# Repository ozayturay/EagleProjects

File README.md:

View this project on [CADLAB.io](https://cadlab.io/project/1437). 

# EagleProjects
Eagle Projects by Özay Turay a.k.a Simon/CGTr

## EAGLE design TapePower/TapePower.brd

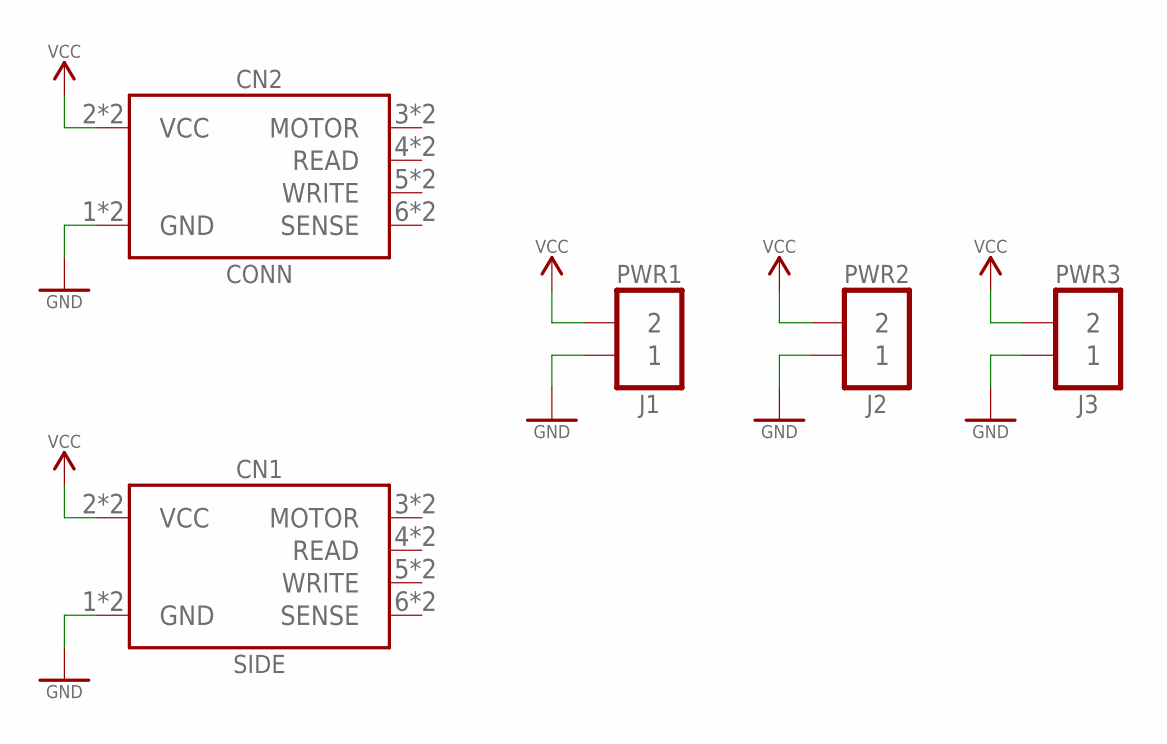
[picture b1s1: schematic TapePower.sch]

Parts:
CN1: SIDE; C64_TAPE_SIDE
CN2: CONN; C64_TAPE_PADS
J1: PWR1; HDR_1X02
J2: PWR2; HDR_1X02
J3: PWR3; HDR_1X02

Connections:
GND: CN1.1 (GND), CN1.A (GND), CN2.1 (GND), CN2.A (GND), J1.1, J2.1, J3.1
VCC: CN1.2 (VCC), CN1.B (VCC), CN2.2 (VCC), CN2.B (VCC), J1.2, J2.2, J3.2

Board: 2 copper layers, 5 parts (0 on the bottom side), 2 nets, no tracks yet.

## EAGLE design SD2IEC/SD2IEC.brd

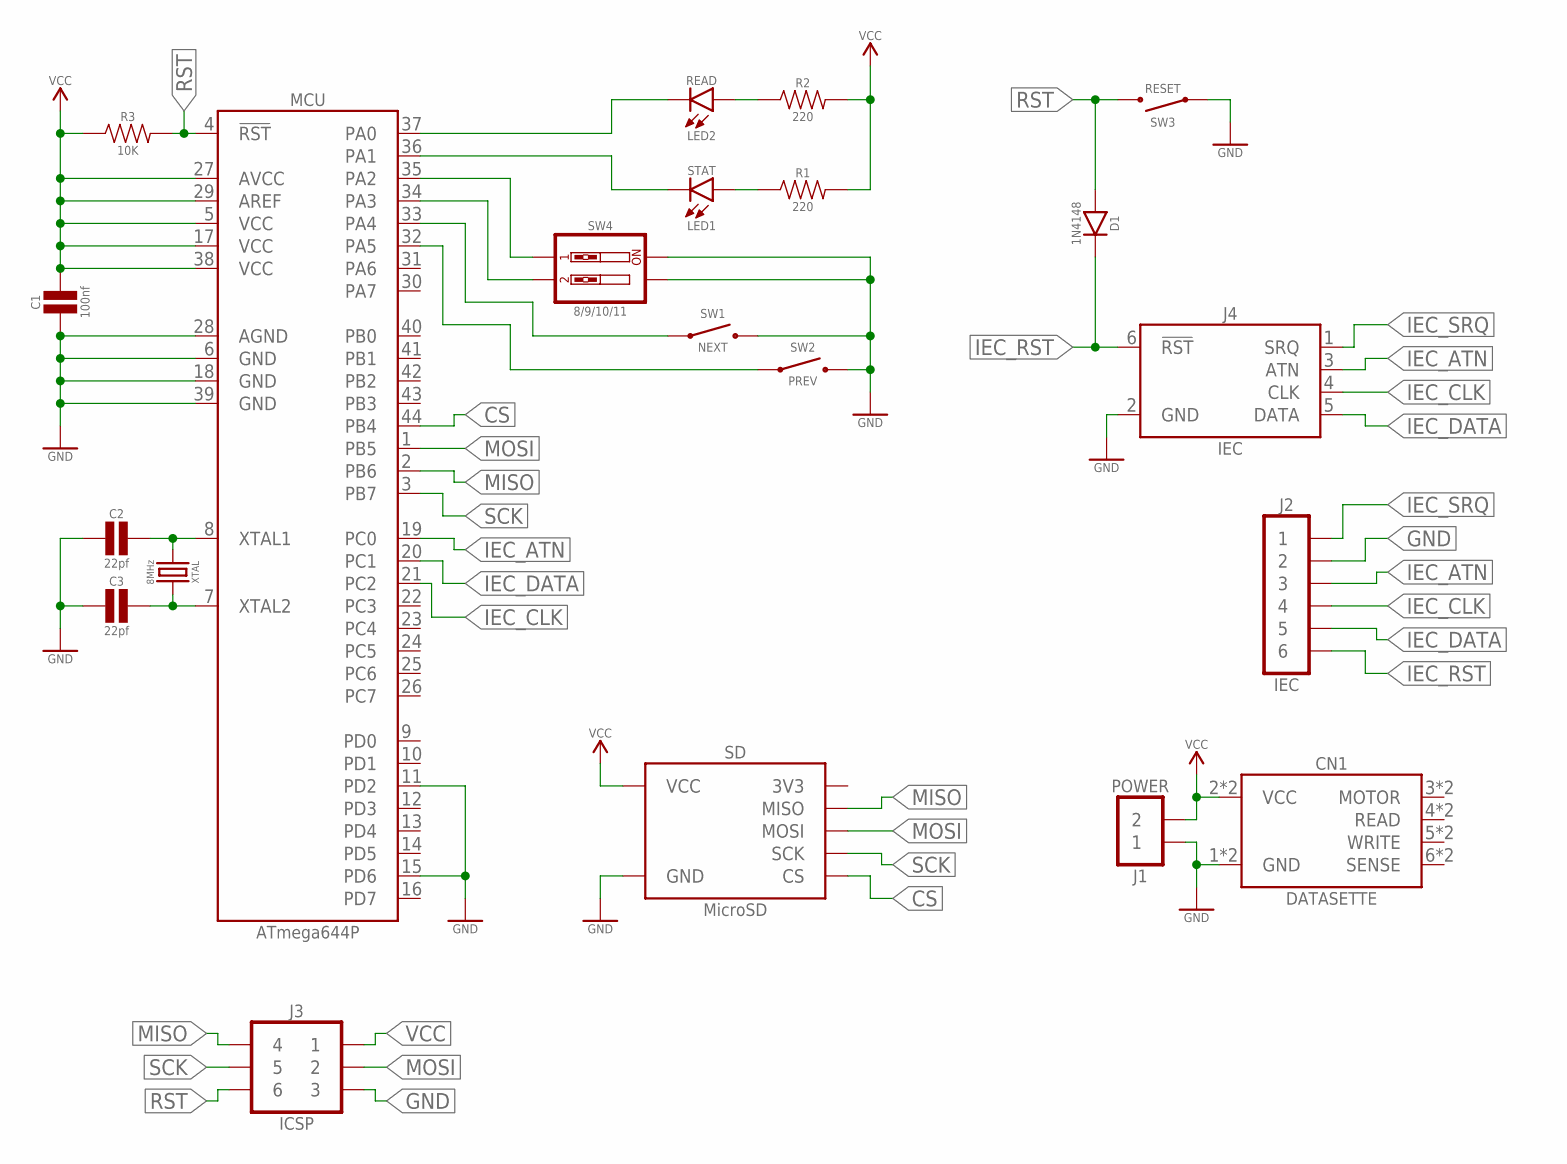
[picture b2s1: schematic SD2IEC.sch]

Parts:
C1: 100nf; CAPACITOR_CERAMIC_1206
C2, C3: 22pf; CAPACITOR_CERAMIC_1206
CN1: DATASETTE; C64_DATASETTE_PADS
D1: 1N4148; DIODE_NORMAL_SMT
J1: POWER; HDR_1X02
J2: IEC; HDR_1X06
J3: ICSP; HDR_2X03
J4: IEC; C64_IEC_DIN6
LED1: STAT; LED_1206
LED2: READ; LED_1206
MCU: ATmega644P; TQFP44
R1, R2: 220; RESISTOR_1206
R3: 10K; RESISTOR_1206
SD: MicroSD; MICROSD_RTL
SW1: NEXT; SWITCH_THT_SIDE
SW2: PREV; SWITCH_THT_SIDE
SW3: RESET; SWITCH_THT_SIDE
SW4: 8/9/10/11; SWITCH_DIP_02
XTAL: 8MHz; XTAL_5032

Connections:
8/9: MCU.35 (PA2), SW4.1
10/11: MCU.34 (PA3), SW4.2
CS: MCU.44 (PB4), SD.CS
GND: C1.1, C2.1, C3.1, CN1.1 (GND), CN1.A (GND), J1.1, J2.2, J3.3, J4.2 (GND), MCU.6 (GND), MCU.11 (PD2), MCU.15 (PD6), MCU.18 (GND), MCU.28 (AGND), MCU.39 (GND), SD.GND, SW1.2, SW2.2, SW3.1, SW4.3, SW4.4
IEC_ATN: J2.3, J4.3 (ATN), MCU.19 (PC0)
IEC_CLK: J2.4, J4.4 (CLK), MCU.21 (PC2)
IEC_DATA: J2.5, J4.5 (DATA), MCU.20 (PC1)
IEC_RST: D1.C (CATHODE), J2.6, J4.6 (!RST)
IEC_SRQ: J2.1, J4.1 (SRQ)
MISO: J3.4, MCU.2 (PB6), SD.MISO
MOSI: J3.2, MCU.1 (PB5), SD.MOSI
NEXT: MCU.33 (PA4), SW1.1
PREV: MCU.32 (PA5), SW2.1
READ: LED2.C, MCU.37 (PA0)
READ1: LED2.A, R2.1
RST: D1.A (ANODE), J3.6, MCU.4 (!RST), R3.2, SW3.2
SCK: J3.5, MCU.3 (PB7), SD.SCK
SELECT: LED1.C, MCU.36 (PA1)
SELECT1: LED1.A, R1.1
VCC: C1.2, CN1.2 (VCC), CN1.B (VCC), J1.2, J3.1, MCU.5 (VCC), MCU.17 (VCC), MCU.27 (AVCC), MCU.29 (AREF), MCU.38 (VCC), R1.2, R2.2, R3.1, SD.VCC
XTAL1: C2.2, MCU.8 (XTAL1), XTAL.1
XTAL2: C3.2, MCU.7 (XTAL2), XTAL.2

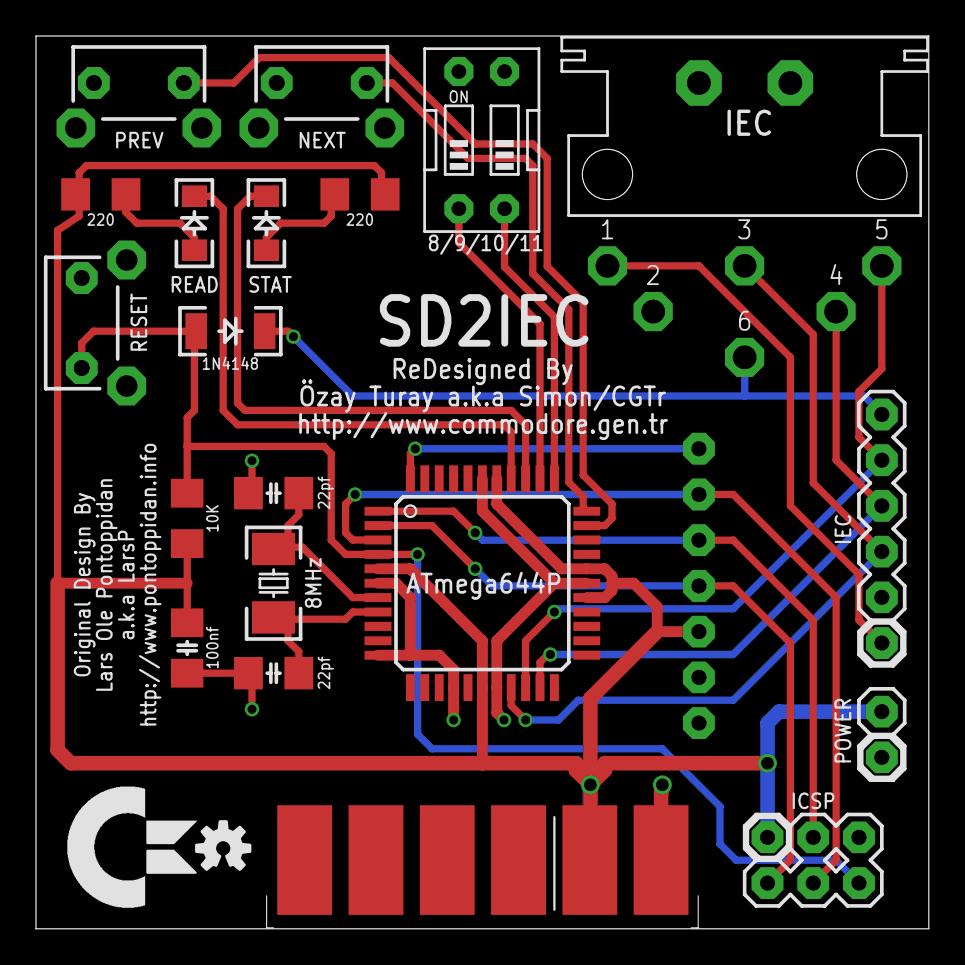
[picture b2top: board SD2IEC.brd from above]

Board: 2 copper layers, 49.6 x 49.6 mm, 22 parts (1 on the bottom side), 22 nets.

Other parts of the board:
LOGO1: OSHW_LOGO_SMALL

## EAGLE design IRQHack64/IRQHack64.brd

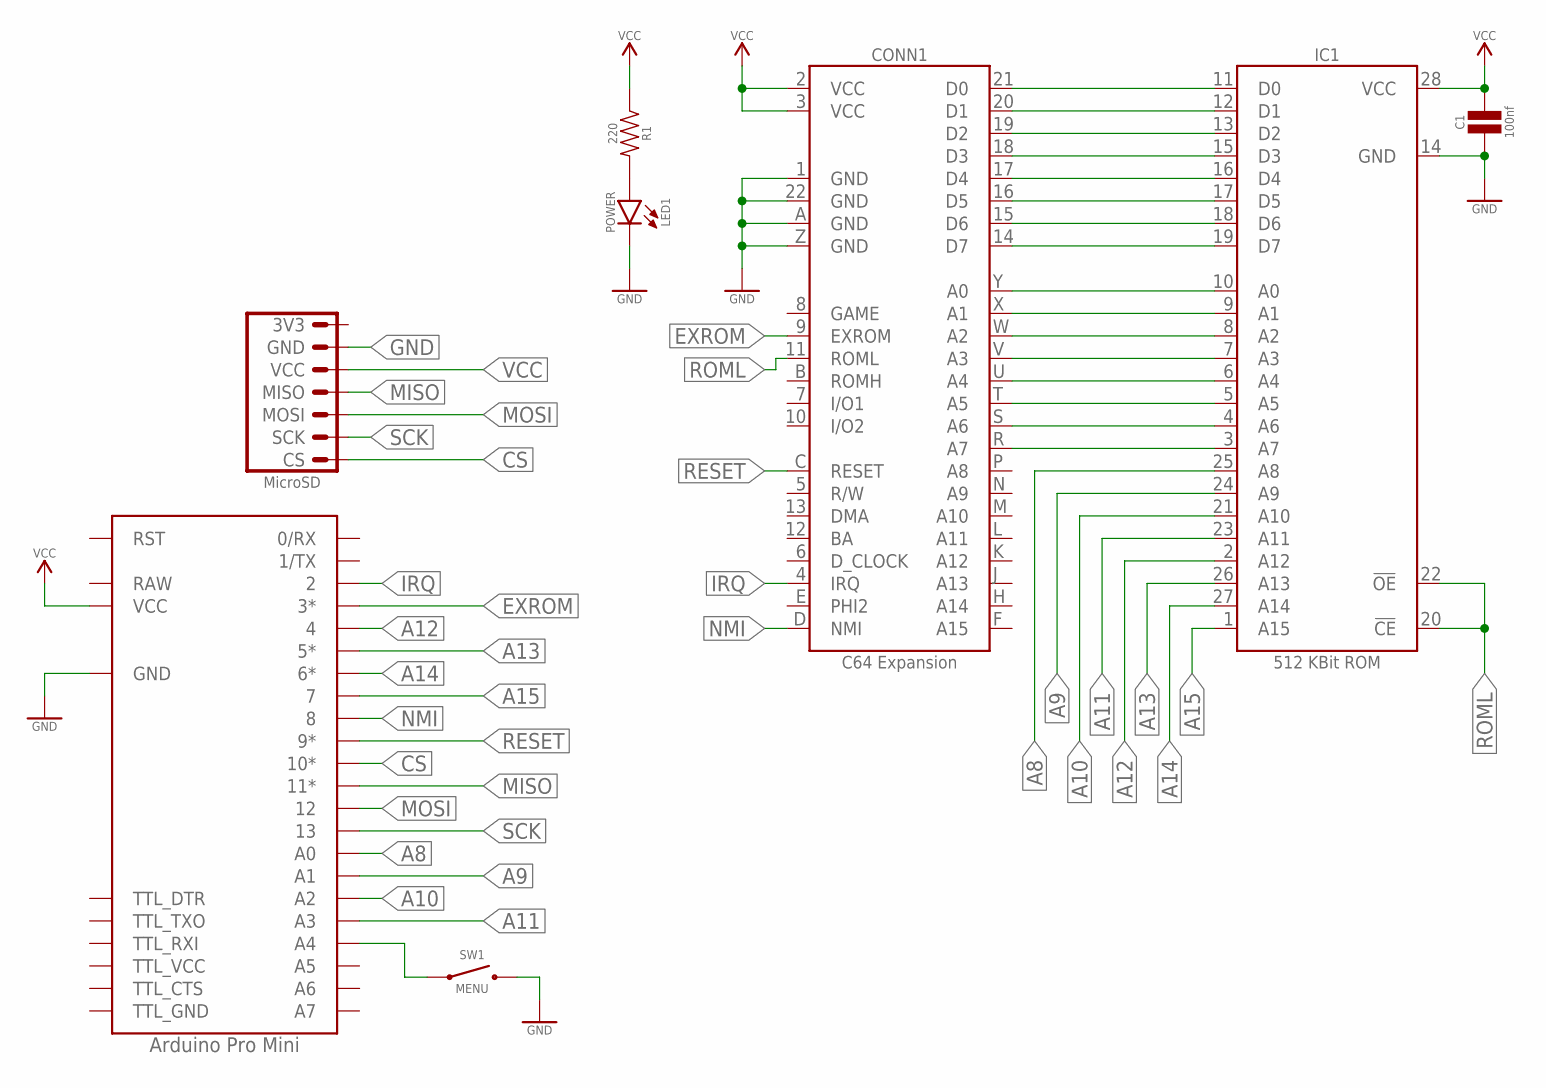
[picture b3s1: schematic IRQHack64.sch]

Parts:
C1: 100nf; CAPACITOR_CERAMIC_0.2
CONN1: C64 Expansion; C64_CARTRIDGE
IC1: 512 KBit ROM; DIP28W
IC2: Arduino Pro Mini; PROMINI
LED1: POWER; LED_03MM
R1: 220; RESISTOR_0.3
SD1: MicroSD; MICROSD_RTL
SW1: MENU; SWITCH_THT_SIDEWITHPADS

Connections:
A0: CONN1.Y (A0), IC1.10 (A0)
A1: CONN1.X (A1), IC1.9 (A1)
A2: CONN1.W (A2), IC1.8 (A2)
A3: CONN1.V (A3), IC1.7 (A3)
A4: CONN1.U (A4), IC1.6 (A4)
A5: CONN1.T (A5), IC1.5 (A5)
A6: CONN1.S (A6), IC1.4 (A6)
A7: CONN1.R (A7), IC1.3 (A7)
A8: IC1.25 (A8), IC2.A0
A9: IC1.24 (A9), IC2.A1
A10: IC1.21 (A10), IC2.A2
A11: IC1.23 (A11), IC2.A3
A12: IC1.2 (A12), IC2.4
A13: IC1.26 (A13), IC2.5*
A14: IC1.27 (A14), IC2.6*
A15: IC1.1 (A15), IC2.7
CS: IC2.10*, SD1.CS
D0: CONN1.21 (D0), IC1.11 (D0)
D1: CONN1.20 (D1), IC1.12 (D1)
D2: CONN1.19 (D2), IC1.13 (D2)
D3: CONN1.18 (D3), IC1.15 (D3)
D4: CONN1.17 (D4), IC1.16 (D4)
D5: CONN1.16 (D5), IC1.17 (D5)
D6: CONN1.15 (D6), IC1.18 (D6)
D7: CONN1.14 (D7), IC1.19 (D7)
EXROM: CONN1.9 (EXROM), IC2.3*
GND: C1.1, CONN1.1 (GND), CONN1.22 (GND), CONN1.A (GND), CONN1.Z (GND), IC1.14 (GND), IC2.GND@1 (GND), IC2.GND@2 (GND), LED1.CATHODE (C), SD1.GND, SW1.2, SW1.BOTTOM (2)
IRQ: CONN1.4 (IRQ), IC2.2
LED0_1: LED1.ANODE (A), R1.2
MENU: IC2.A4@1 (A4), IC2.A4@2 (A4), SW1.1, SW1.TOP (1)
MISO: IC2.11*, SD1.MISO
MOSI: IC2.12, SD1.MOSI
NMI: CONN1.D (NMI), IC2.8
RESET: CONN1.C (RESET), IC2.9*
ROML: CONN1.11 (ROML), IC1.20 (!CE), IC1.22 (!OE)
SCK: IC2.13, SD1.SCK
VCC: C1.2, CONN1.2 (VCC), CONN1.3 (VCC), IC1.28 (VCC), IC2.VCC, R1.1, SD1.VCC

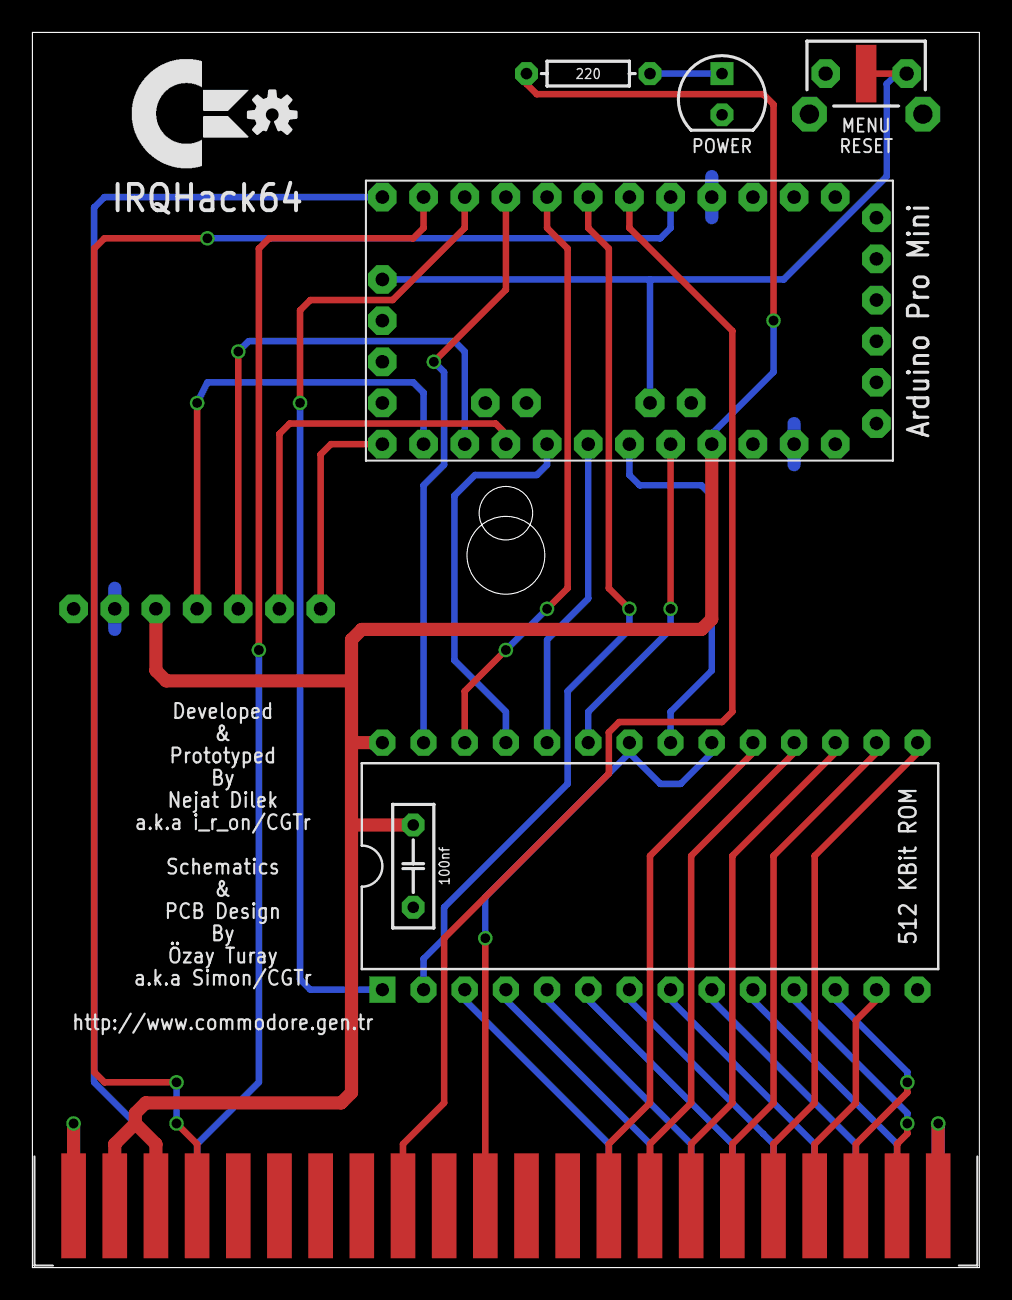
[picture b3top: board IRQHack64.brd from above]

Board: 2 copper layers, 58.4 x 76.2 mm, 9 parts (1 on the bottom side), 37 nets.

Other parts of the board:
LOGO1: OSHW_LOGO_SMALL

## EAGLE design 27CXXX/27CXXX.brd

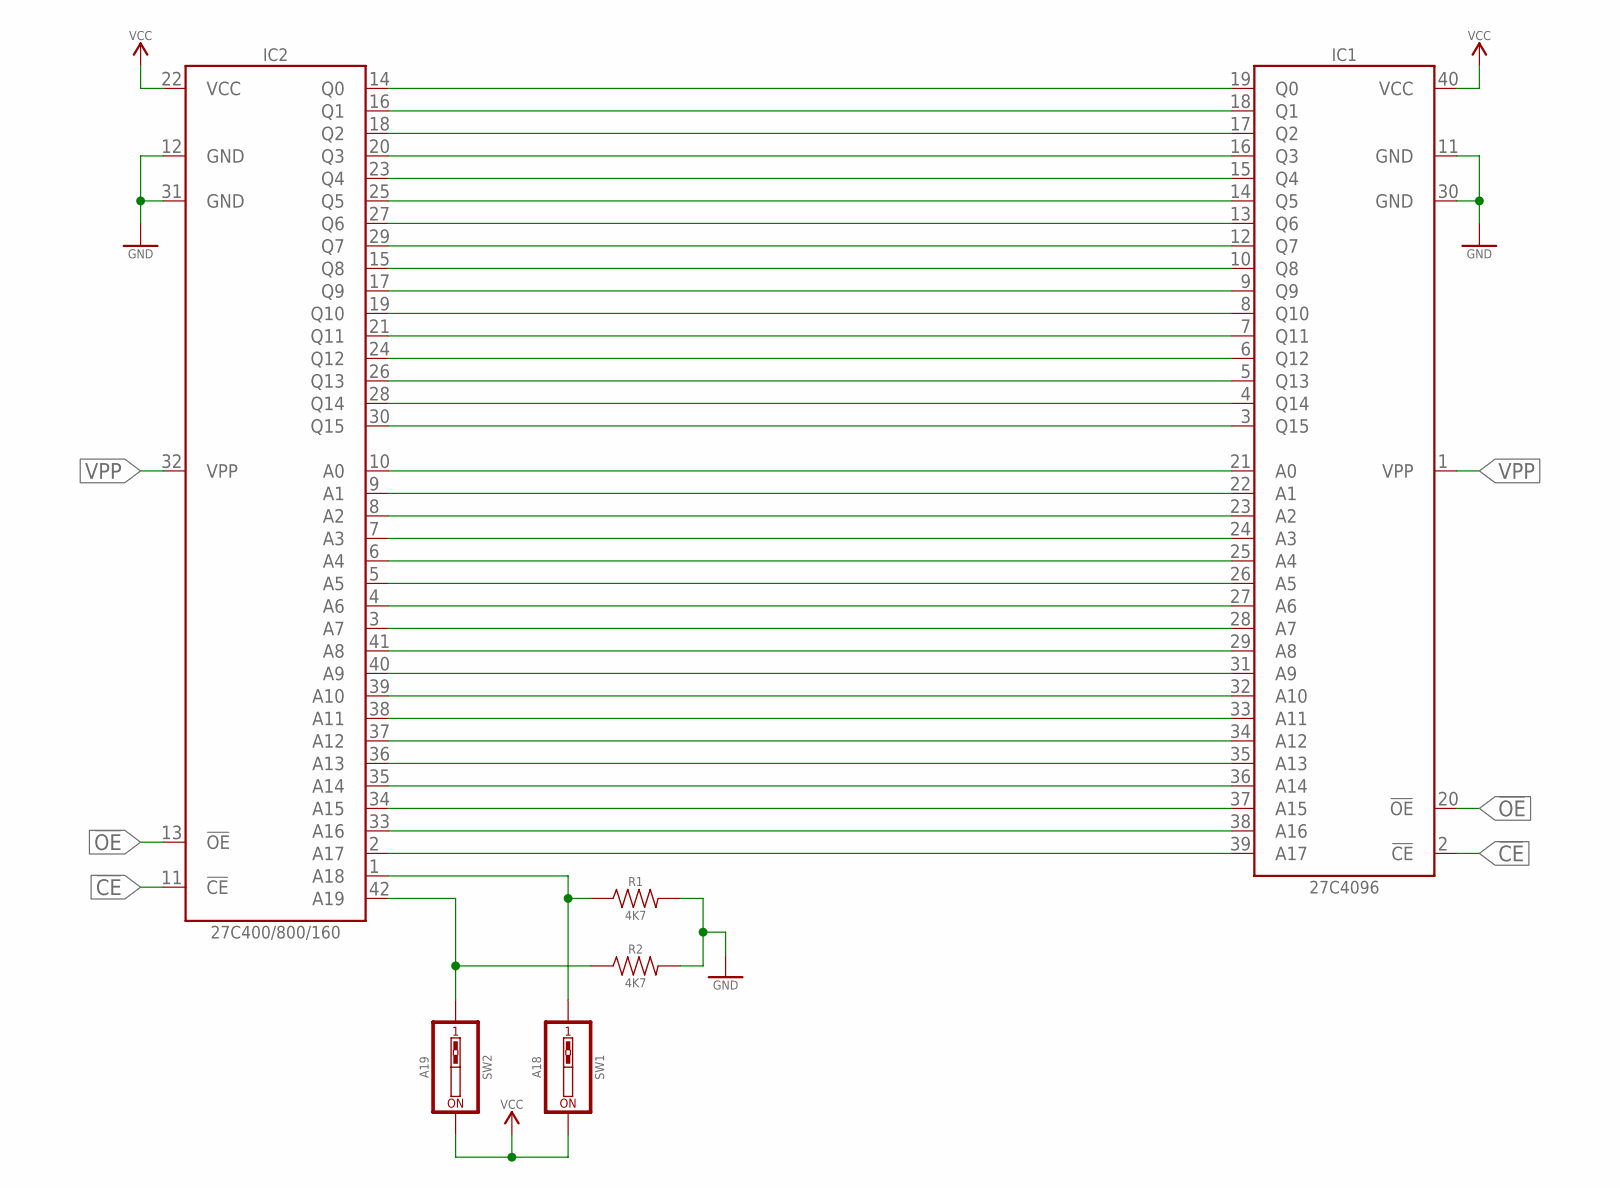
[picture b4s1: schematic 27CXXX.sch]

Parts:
IC1: 27C4096; DIP40W
IC2: 27C400/800/160; ZIF42F
R1, R2: 4K7; RESISTOR_0.3
SW1: A18; SWITCH_DIP_01
SW2: A19; SWITCH_DIP_01

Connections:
!CE: IC1.2 (!CE), IC2.11 (!CE)
!OE: IC1.20 (!OE), IC2.13 (!OE)
A0: IC1.21 (A0), IC2.10 (A0)
A1: IC1.22 (A1), IC2.9 (A1)
A2: IC1.23 (A2), IC2.8 (A2)
A3: IC1.24 (A3), IC2.7 (A3)
A4: IC1.25 (A4), IC2.6 (A4)
A5: IC1.26 (A5), IC2.5 (A5)
A6: IC1.27 (A6), IC2.4 (A6)
A7: IC1.28 (A7), IC2.3 (A7)
A8: IC1.29 (A8), IC2.41 (A8)
A9: IC1.31 (A9), IC2.40 (A9)
A10: IC1.32 (A10), IC2.39 (A10)
A11: IC1.33 (A11), IC2.38 (A11)
A12: IC1.34 (A12), IC2.37 (A12)
A13: IC1.35 (A13), IC2.36 (A13)
A14: IC1.36 (A14), IC2.35 (A14)
A15: IC1.37 (A15), IC2.34 (A15)
A16: IC1.38 (A16), IC2.33 (A16)
A17: IC1.39 (A17), IC2.2 (A17)
A18: IC2.1 (A18), R1.1, SW1.1
A19: IC2.42 (A19), R2.1, SW2.1
GND: IC1.11 (GND), IC1.30 (GND), IC2.12 (GND), IC2.31 (GND), R1.2, R2.2
Q0: IC1.19 (Q0), IC2.14 (Q0)
Q1: IC1.18 (Q1), IC2.16 (Q1)
Q2: IC1.17 (Q2), IC2.18 (Q2)
Q3: IC1.16 (Q3), IC2.20 (Q3)
Q4: IC1.15 (Q4), IC2.23 (Q4)
Q5: IC1.14 (Q5), IC2.25 (Q5)
Q6: IC1.13 (Q6), IC2.27 (Q6)
Q7: IC1.12 (Q7), IC2.29 (Q7)
Q8: IC1.10 (Q8), IC2.15 (Q8)
Q9: IC1.9 (Q9), IC2.17 (Q9)
Q10: IC1.8 (Q10), IC2.19 (Q10)
Q11: IC1.7 (Q11), IC2.21 (Q11)
Q12: IC1.6 (Q12), IC2.24 (Q12)
Q13: IC1.5 (Q13), IC2.26 (Q13)
Q14: IC1.4 (Q14), IC2.28 (Q14)
Q15: IC1.3 (Q15), IC2.30 (Q15)
VCC: IC1.40 (VCC), IC2.22 (VCC), SW1.2, SW2.2
VPP: IC1.1 (VPP), IC2.32 (VPP)

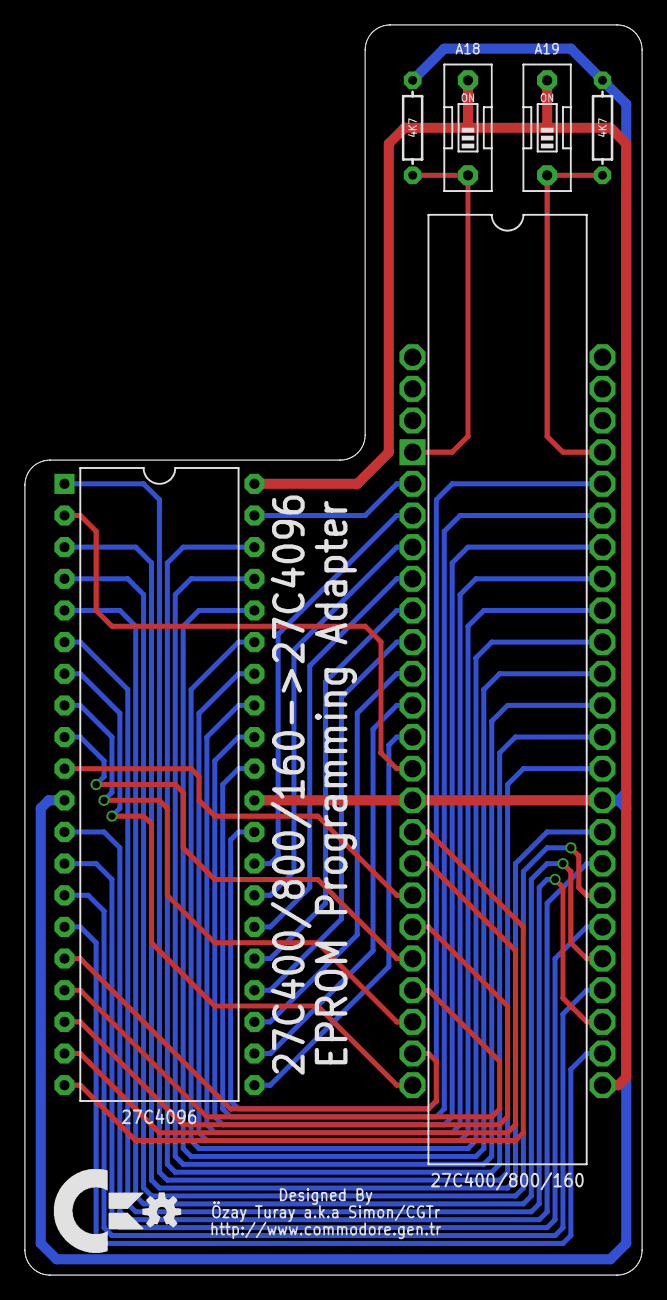
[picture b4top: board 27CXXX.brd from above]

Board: 2 copper layers, 49.5 x 100.3 mm, 7 parts (0 on the bottom side), 41 nets.

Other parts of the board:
LOGO1: OSHW_LOGO_SMALL

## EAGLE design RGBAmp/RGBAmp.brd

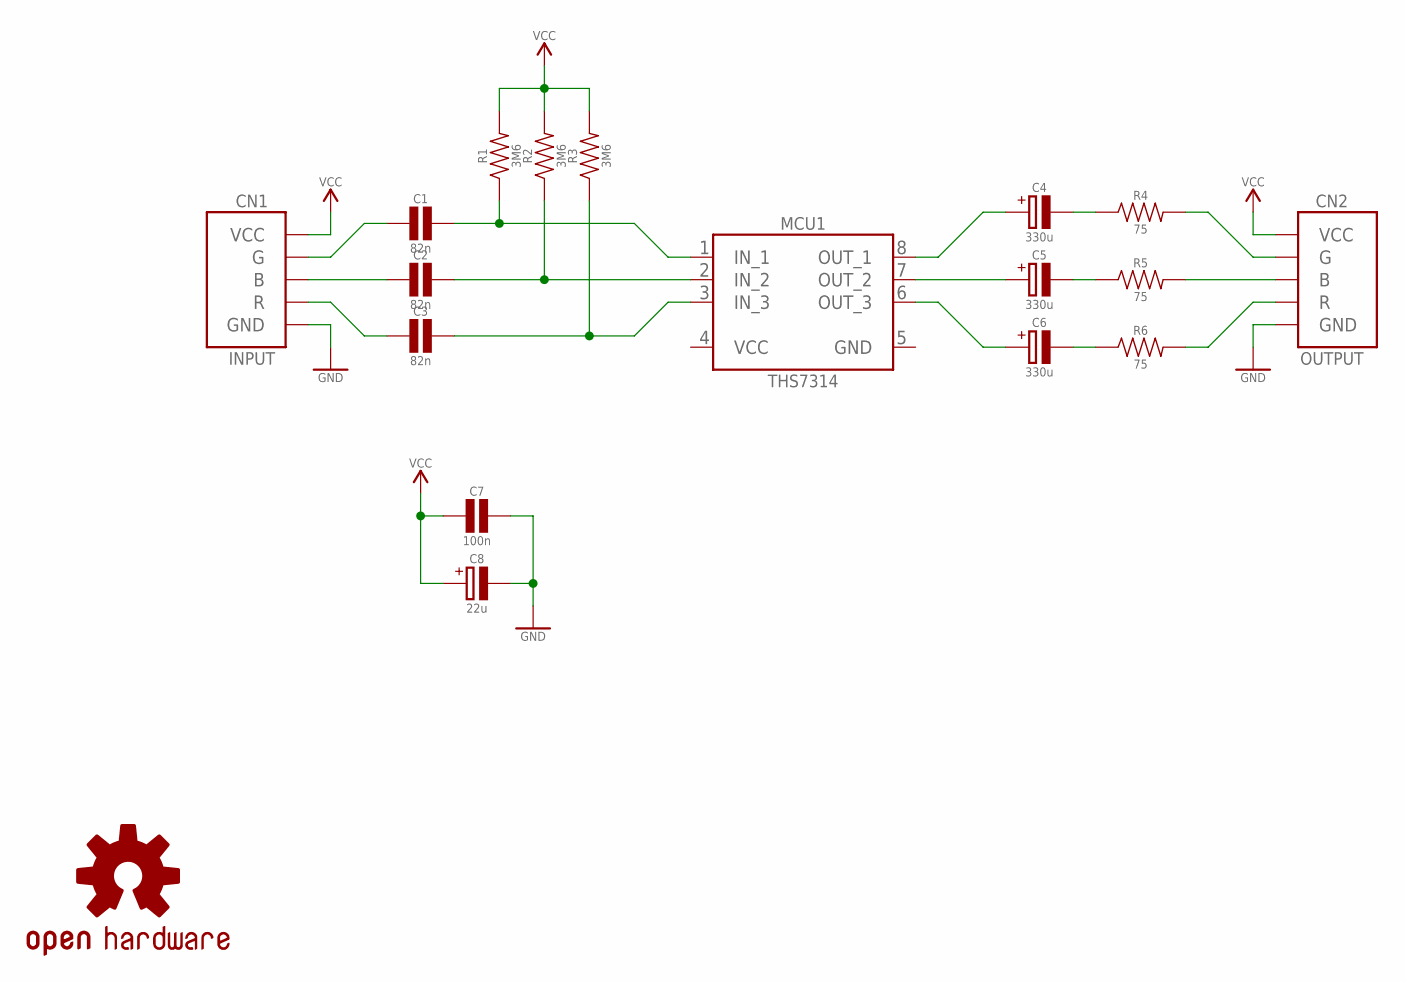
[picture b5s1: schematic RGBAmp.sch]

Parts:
C1, C2, C3: 82n; CAPACITOR_CERAMIC_1206
C4, C5, C6: 330u; CAPACITOR_POLARIZED_6.3X7.7
C7: 100n; CAPACITOR_CERAMIC_1206
C8: 22u; CAPACITOR_POLARIZED_6.3X7.7
CN1: INPUT; GBR_PADS
CN2: OUTPUT; GBR_PADS
LOGO1: OSHW_LOGO_SMALL
MCU1: THS7314; SOP08
R1, R2, R3: 3M6; RESISTOR_1206
R4, R5, R6: 75; RESISTOR_1206

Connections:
GND: C7.2, C8.-, CN1.GND, CN2.GND, MCU1.5 (GND)
unnamed: C1.2, MCU1.1 (IN_1), R1.1
unnamed: C2.2, MCU1.2 (IN_2), R2.1
unnamed: C3.2, MCU1.3 (IN_3), R3.1
unnamed: C2.1, CN1.B
unnamed: C1.1, CN1.G
unnamed: C3.1, CN1.R
unnamed: C4.+, MCU1.8 (OUT_1)
unnamed: C5.+, MCU1.7 (OUT_2)
unnamed: C6.+, MCU1.6 (OUT_3)
unnamed: C4.-, R4.1
unnamed: C5.-, R5.1
unnamed: C6.-, R6.1
unnamed: CN2.G, R4.2
unnamed: CN2.B, R5.2
unnamed: CN2.R, R6.2
VCC: C7.1, C8.+, CN1.VCC, CN2.VCC, MCU1.4 (VCC), R1.2, R2.2, R3.2

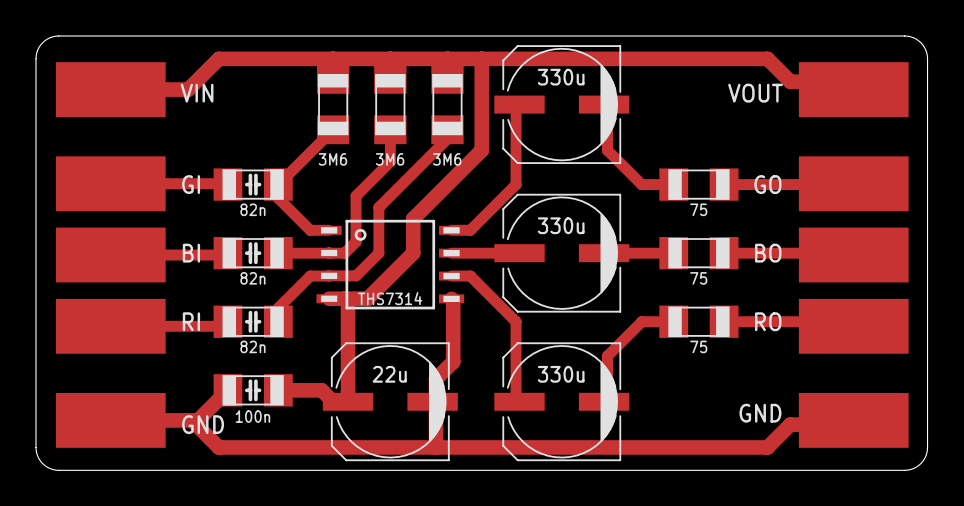
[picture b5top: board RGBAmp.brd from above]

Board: 2 copper layers, 49.5 x 24.1 mm, 18 parts (1 on the bottom side), 17 nets.

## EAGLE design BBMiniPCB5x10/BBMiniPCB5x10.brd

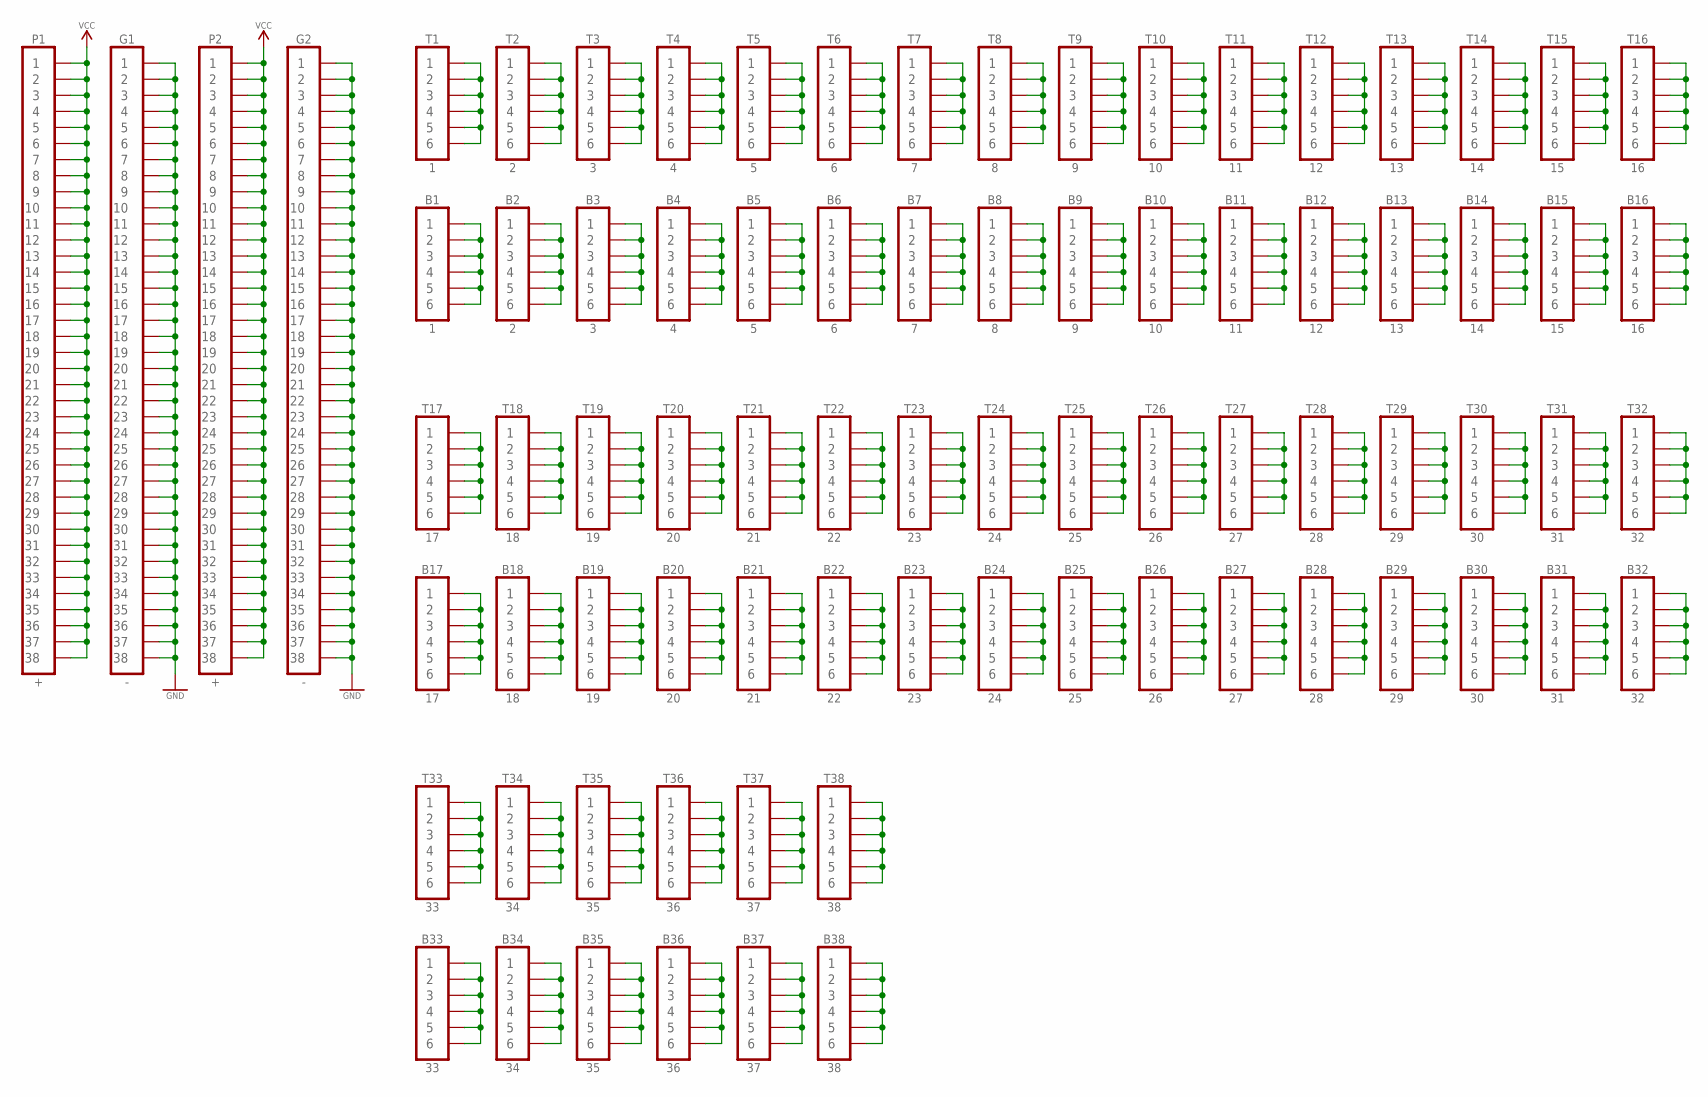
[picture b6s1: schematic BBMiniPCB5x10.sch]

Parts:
B1: 1; HDR_1X06_NOSILK
B2: 2; HDR_1X06_NOSILK
B3: 3; HDR_1X06_NOSILK
B4: 4; HDR_1X06_NOSILK
B5: 5; HDR_1X06_NOSILK
B6: 6; HDR_1X06_NOSILK
B7: 7; HDR_1X06_NOSILK
B8: 8; HDR_1X06_NOSILK
B9: 9; HDR_1X06_NOSILK
B10: 10; HDR_1X06_NOSILK
B11: 11; HDR_1X06_NOSILK
B12: 12; HDR_1X06_NOSILK
B13: 13; HDR_1X06_NOSILK
B14: 14; HDR_1X06_NOSILK
B15: 15; HDR_1X06_NOSILK
B16: 16; HDR_1X06_NOSILK
B17: 17; HDR_1X06_NOSILK
B18: 18; HDR_1X06_NOSILK
B19: 19; HDR_1X06_NOSILK
B20: 20; HDR_1X06_NOSILK
B21: 21; HDR_1X06_NOSILK
B22: 22; HDR_1X06_NOSILK
B23: 23; HDR_1X06_NOSILK
B24: 24; HDR_1X06_NOSILK
B25: 25; HDR_1X06_NOSILK
B26: 26; HDR_1X06_NOSILK
B27: 27; HDR_1X06_NOSILK
B28: 28; HDR_1X06_NOSILK
B29: 29; HDR_1X06_NOSILK
B30: 30; HDR_1X06_NOSILK
B31: 31; HDR_1X06_NOSILK
B32: 32; HDR_1X06_NOSILK
B33: 33; HDR_1X06_NOSILK
B34: 34; HDR_1X06_NOSILK
B35: 35; HDR_1X06_NOSILK
B36: 36; HDR_1X06_NOSILK
B37: 37; HDR_1X06_NOSILK
B38: 38; HDR_1X06_NOSILK
G1, G2: -; HDR_1X38_NOSILK
P1, P2: +; HDR_1X38_NOSILK
T1: 1; HDR_1X06_NOSILK
T2: 2; HDR_1X06_NOSILK
T3: 3; HDR_1X06_NOSILK
T4: 4; HDR_1X06_NOSILK
T5: 5; HDR_1X06_NOSILK
T6: 6; HDR_1X06_NOSILK
T7: 7; HDR_1X06_NOSILK
T8: 8; HDR_1X06_NOSILK
T9: 9; HDR_1X06_NOSILK
T10: 10; HDR_1X06_NOSILK
T11: 11; HDR_1X06_NOSILK
T12: 12; HDR_1X06_NOSILK
T13: 13; HDR_1X06_NOSILK
T14: 14; HDR_1X06_NOSILK
T15: 15; HDR_1X06_NOSILK
T16: 16; HDR_1X06_NOSILK
T17: 17; HDR_1X06_NOSILK
T18: 18; HDR_1X06_NOSILK
T19: 19; HDR_1X06_NOSILK
T20: 20; HDR_1X06_NOSILK
T21: 21; HDR_1X06_NOSILK
T22: 22; HDR_1X06_NOSILK
T23: 23; HDR_1X06_NOSILK
T24: 24; HDR_1X06_NOSILK
T25: 25; HDR_1X06_NOSILK
T26: 26; HDR_1X06_NOSILK
T27: 27; HDR_1X06_NOSILK
T28: 28; HDR_1X06_NOSILK
T29: 29; HDR_1X06_NOSILK
T30: 30; HDR_1X06_NOSILK
T31: 31; HDR_1X06_NOSILK
T32: 32; HDR_1X06_NOSILK
T33: 33; HDR_1X06_NOSILK
T34: 34; HDR_1X06_NOSILK
T35: 35; HDR_1X06_NOSILK
T36: 36; HDR_1X06_NOSILK
T37: 37; HDR_1X06_NOSILK
T38: 38; HDR_1X06_NOSILK

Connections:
B1: B1.1, B1.2, B1.3, B1.4, B1.5, B1.6
B2: B2.1, B2.2, B2.3, B2.4, B2.5, B2.6
B3: B3.1, B3.2, B3.3, B3.4, B3.5, B3.6
B4: B4.1, B4.2, B4.3, B4.4, B4.5, B4.6
B5: B5.1, B5.2, B5.3, B5.4, B5.5, B5.6
B6: B6.1, B6.2, B6.3, B6.4, B6.5, B6.6
B7: B7.1, B7.2, B7.3, B7.4, B7.5, B7.6
B8: B8.1, B8.2, B8.3, B8.4, B8.5, B8.6
B9: B9.1, B9.2, B9.3, B9.4, B9.5, B9.6
B10: B10.1, B10.2, B10.3, B10.4, B10.5, B10.6
B11: B11.1, B11.2, B11.3, B11.4, B11.5, B11.6
B12: B12.1, B12.2, B12.3, B12.4, B12.5, B12.6
B13: B13.1, B13.2, B13.3, B13.4, B13.5, B13.6
B14: B14.1, B14.2, B14.3, B14.4, B14.5, B14.6
B15: B15.1, B15.2, B15.3, B15.4, B15.5, B15.6
B16: B16.1, B16.2, B16.3, B16.4, B16.5, B16.6
B17: B17.1, B17.2, B17.3, B17.4, B17.5, B17.6
B18: B18.1, B18.2, B18.3, B18.4, B18.5, B18.6
B19: B19.1, B19.2, B19.3, B19.4, B19.5, B19.6
B20: B20.1, B20.2, B20.3, B20.4, B20.5, B20.6
B21: B21.1, B21.2, B21.3, B21.4, B21.5, B21.6
B22: B22.1, B22.2, B22.3, B22.4, B22.5, B22.6
B23: B23.1, B23.2, B23.3, B23.4, B23.5, B23.6
B24: B24.1, B24.2, B24.3, B24.4, B24.5, B24.6
B25: B25.1, B25.2, B25.3, B25.4, B25.5, B25.6
B26: B26.1, B26.2, B26.3, B26.4, B26.5, B26.6
B27: B27.1, B27.2, B27.3, B27.4, B27.5, B27.6
B28: B28.1, B28.2, B28.3, B28.4, B28.5, B28.6
B29: B29.1, B29.2, B29.3, B29.4, B29.5, B29.6
B30: B30.1, B30.2, B30.3, B30.4, B30.5, B30.6
B31: B31.1, B31.2, B31.3, B31.4, B31.5, B31.6
B32: B32.1, B32.2, B32.3, B32.4, B32.5, B32.6
B33: B33.1, B33.2, B33.3, B33.4, B33.5, B33.6
B34: B34.1, B34.2, B34.3, B34.4, B34.5, B34.6
B35: B35.1, B35.2, B35.3, B35.4, B35.5, B35.6
B36: B36.1, B36.2, B36.3, B36.4, B36.5, B36.6
B37: B37.1, B37.2, B37.3, B37.4, B37.5, B37.6
B38: B38.1, B38.2, B38.3, B38.4, B38.5, B38.6
GND: G1.1, G1.2, G1.3, G1.4, G1.5, G1.6, G1.7, G1.8, G1.9, G1.10, G1.11, G1.12, G1.13, G1.14, G1.15, G1.16, G1.17, G1.18, G1.19, G1.20, G1.21, G1.22, G1.23, G1.24, G1.25, G1.26, G1.27, G1.28, G1.29, G1.30, G1.31, G1.32, G1.33, G1.34, G1.35, G1.36, G1.37, G1.38, G2.1, G2.2, G2.3, G2.4, G2.5, G2.6, G2.7, G2.8, G2.9, G2.10, G2.11, G2.12, G2.13, G2.14, G2.15, G2.16, G2.17, G2.18, G2.19, G2.20, G2.21, G2.22, G2.23, G2.24, G2.25, G2.26, G2.27, G2.28, G2.29, G2.30, G2.31, G2.32, G2.33, G2.34, G2.35, G2.36, G2.37, G2.38
T1: T1.1, T1.2, T1.3, T1.4, T1.5, T1.6
T2: T2.1, T2.2, T2.3, T2.4, T2.5, T2.6
T3: T3.1, T3.2, T3.3, T3.4, T3.5, T3.6
T4: T4.1, T4.2, T4.3, T4.4, T4.5, T4.6
T5: T5.1, T5.2, T5.3, T5.4, T5.5, T5.6
T6: T6.1, T6.2, T6.3, T6.4, T6.5, T6.6
T7: T7.1, T7.2, T7.3, T7.4, T7.5, T7.6
T8: T8.1, T8.2, T8.3, T8.4, T8.5, T8.6
T9: T9.1, T9.2, T9.3, T9.4, T9.5, T9.6
T10: T10.1, T10.2, T10.3, T10.4, T10.5, T10.6
T11: T11.1, T11.2, T11.3, T11.4, T11.5, T11.6
T12: T12.1, T12.2, T12.3, T12.4, T12.5, T12.6
T13: T13.1, T13.2, T13.3, T13.4, T13.5, T13.6
T14: T14.1, T14.2, T14.3, T14.4, T14.5, T14.6
T15: T15.1, T15.2, T15.3, T15.4, T15.5, T15.6
T16: T16.1, T16.2, T16.3, T16.4, T16.5, T16.6
T17: T17.1, T17.2, T17.3, T17.4, T17.5, T17.6
T18: T18.1, T18.2, T18.3, T18.4, T18.5, T18.6
T19: T19.1, T19.2, T19.3, T19.4, T19.5, T19.6
T20: T20.1, T20.2, T20.3, T20.4, T20.5, T20.6
T21: T21.1, T21.2, T21.3, T21.4, T21.5, T21.6
T22: T22.1, T22.2, T22.3, T22.4, T22.5, T22.6
T23: T23.1, T23.2, T23.3, T23.4, T23.5, T23.6
T24: T24.1, T24.2, T24.3, T24.4, T24.5, T24.6
T25: T25.1, T25.2, T25.3, T25.4, T25.5, T25.6
T26: T26.1, T26.2, T26.3, T26.4, T26.5, T26.6
T27: T27.1, T27.2, T27.3, T27.4, T27.5, T27.6
T28: T28.1, T28.2, T28.3, T28.4, T28.5, T28.6
T29: T29.1, T29.2, T29.3, T29.4, T29.5, T29.6
T30: T30.1, T30.2, T30.3, T30.4, T30.5, T30.6
T31: T31.1, T31.2, T31.3, T31.4, T31.5, T31.6
T32: T32.1, T32.2, T32.3, T32.4, T32.5, T32.6
T33: T33.1, T33.2, T33.3, T33.4, T33.5, T33.6
T34: T34.1, T34.2, T34.3, T34.4, T34.5, T34.6
T35: T35.1, T35.2, T35.3, T35.4, T35.5, T35.6
T36: T36.1, T36.2, T36.3, T36.4, T36.5, T36.6
T37: T37.1, T37.2, T37.3, T37.4, T37.5, T37.6
T38: T38.1, T38.2, T38.3, T38.4, T38.5, T38.6
VCC: P1.1, P1.2, P1.3, P1.4, P1.5, P1.6, P1.7, P1.8, P1.9, P1.10, P1.11, P1.12, P1.13, P1.14, P1.15, P1.16, P1.17, P1.18, P1.19, P1.20, P1.21, P1.22, P1.23, P1.24, P1.25, P1.26, P1.27, P1.28, P1.29, P1.30, P1.31, P1.32, P1.33, P1.34, P1.35, P1.36, P1.37, P1.38, P2.1, P2.2, P2.3, P2.4, P2.5, P2.6, P2.7, P2.8, P2.9, P2.10, P2.11, P2.12, P2.13, P2.14, P2.15, P2.16, P2.17, P2.18, P2.19, P2.20, P2.21, P2.22, P2.23, P2.24, P2.25, P2.26, P2.27, P2.28, P2.29, P2.30, P2.31, P2.32, P2.33, P2.34, P2.35, P2.36, P2.37, P2.38

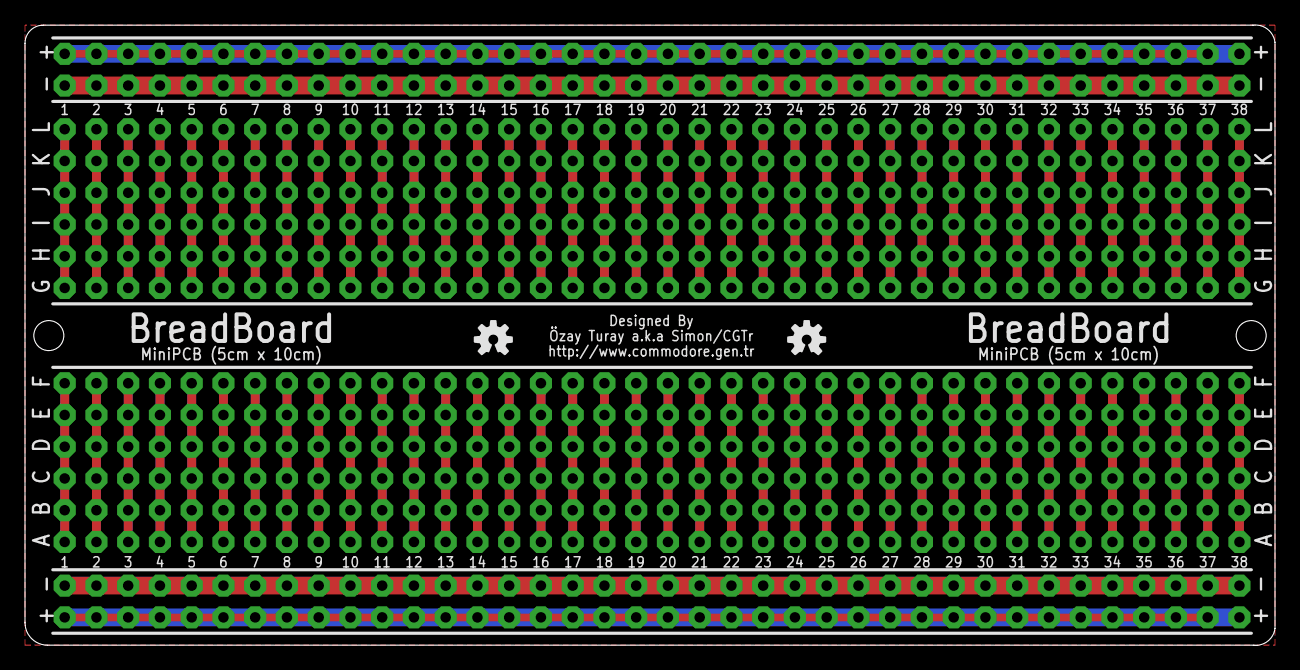
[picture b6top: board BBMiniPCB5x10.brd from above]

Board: 2 copper layers, 100.0 x 49.6 mm, 82 parts (0 on the bottom side), 78 nets.

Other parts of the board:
LOGO1, LOGO2: OSHW_LOGO_SMALL
